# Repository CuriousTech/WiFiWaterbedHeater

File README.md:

# WiFi Smart Waterbed Heater

Discontinued years ago. Go here: [WiFiWaterbedHeater3](https://github.com/CuriousTech/WiFiWaterbedHeater3)

Original model:  

SSR model:

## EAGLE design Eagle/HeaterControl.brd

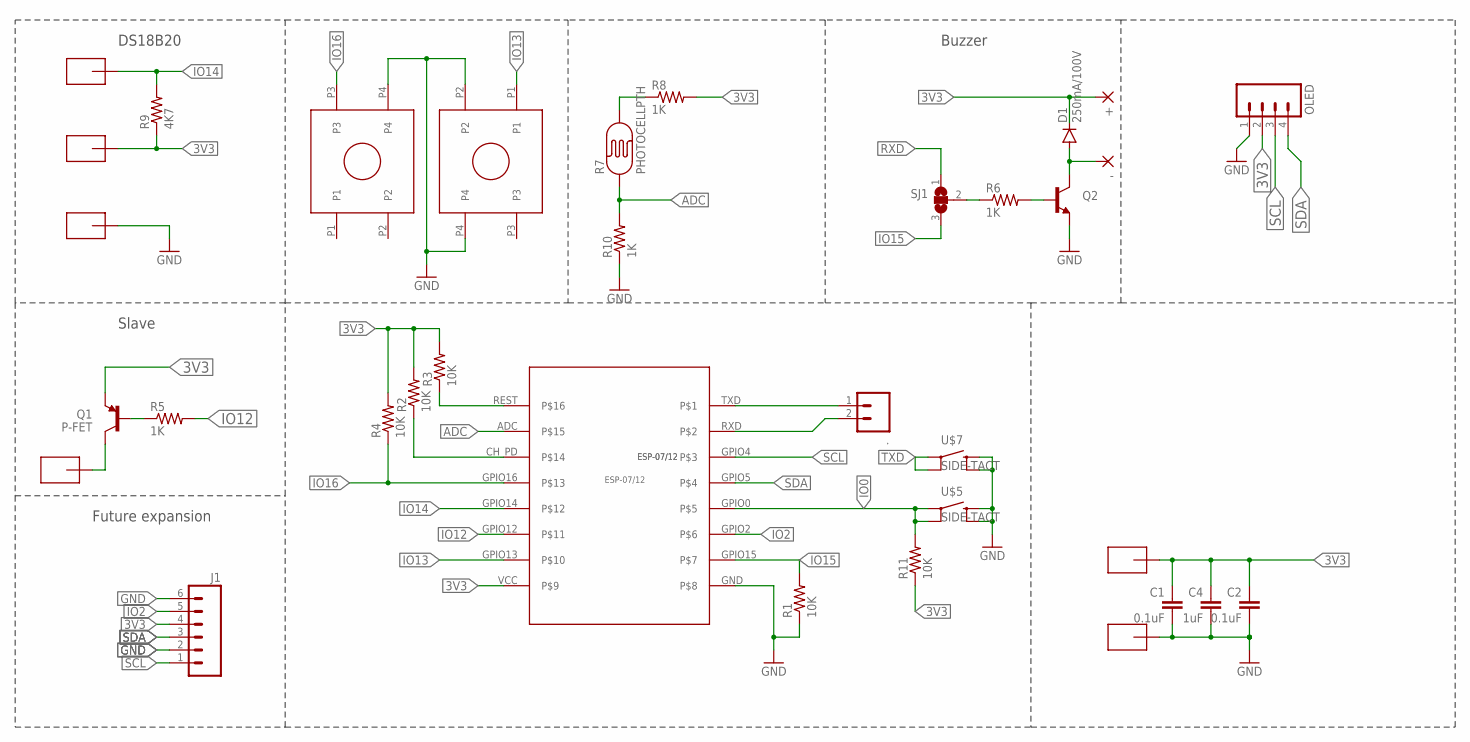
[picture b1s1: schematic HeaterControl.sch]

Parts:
+: 1,6/0,8
-: 1,6/0,8
.: M02PTH; 1X02
C1, C2: 0.1uF; 0805-CAP
C4: 1uF; 0805-CAP
D1: 250mA/100V; SOD-323
J1: M06SILK_FEMALE_PTH; 1X06
LEFT: OMROM_TH
OLED: M04PTH; 1X04
Q1: P-FET; SOT23-3
Q2: TRANSISTOR_NPNSOT23-3; SOT23-3
R1, R2, R3, R4, R11: 10K; 0805
R5, R6, R8, R10: 1K; 0805
R7: PHOTOCELLPTH; PHOTOCELL
R9: 4K7; 0805
RIGHT: OMROM_TH
SJ1: SJ2W; SJ_2
U$1: ESP-07/12
U$2, U$3, U$6, U$8, U$10, U$11: SMD-PAD1
U$5, U$7: SIDE-TACT

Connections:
3V3: +.1, C1.1, C2.1, C4.1, D1.C, J1.4, OLED.2, Q1.2 (E), R2.2, R3.2, R4.2, R8.2, R9.1, R11.1, U$1.VCC, U$3.>NAME, U$8.>NAME
ADC: R7.1, R10.2, U$1.ADC
GND: C1.2, C2.2, C4.2, J1.2, J1.6, LEFT.P4, OLED.1, Q2.2 (E), R1.1, R10.1, RIGHT.P2, RIGHT.P4, U$1.GND, U$5.3 (2), U$5.4, U$6.>NAME, U$7.3 (2), U$7.4, U$11.>NAME
IO0: R11.2, U$1.GPIO0, U$5.1, U$5.2 (3)
IO2: J1.5, U$1.GPIO2
IO12: R5.2, U$1.GPIO12
IO13: RIGHT.P1, U$1.GPIO13
IO14: R9.2, U$1.GPIO14, U$10.>NAME
IO15: R1.2, SJ1.3, U$1.GPIO15
IO16: LEFT.P3, R4.1, U$1.GPIO16
unnamed: Q1.3 (C), U$2.>NAME
unnamed: Q2.1 (B), R6.2
unnamed: -.1, D1.A, Q2.3 (C)
unnamed: R7.2, R8.1
unnamed: Q1.1 (B), R5.1
unnamed: R6.1, SJ1.2
unnamed: R2.1, U$1.CH_PD
REST: R3.1, U$1.REST
RXD: ..2, SJ1.1, U$1.RXD
SCL: J1.1, OLED.3, U$1.GPIO4
SDA: J1.3, OLED.4, U$1.GPIO5
TXD: ..1, U$1.TXD, U$7.1, U$7.2 (3)

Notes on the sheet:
DS18B20
Slave
Buzzer
Future expansion

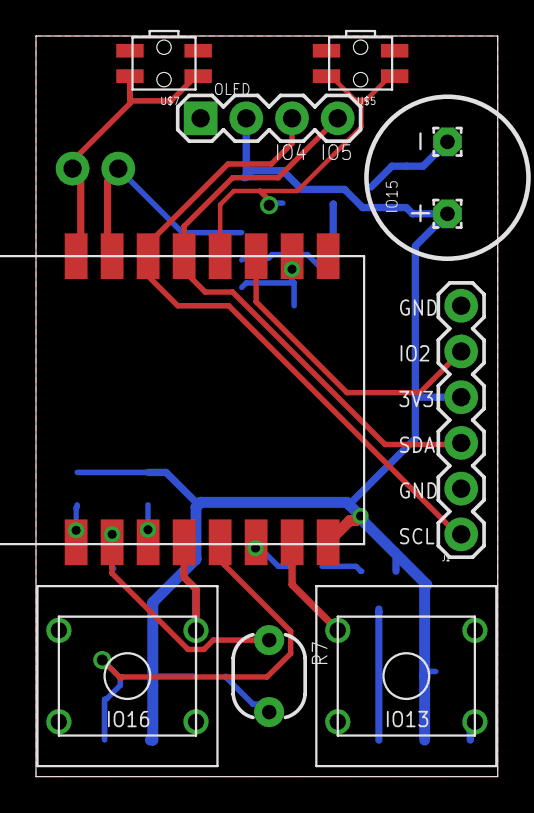
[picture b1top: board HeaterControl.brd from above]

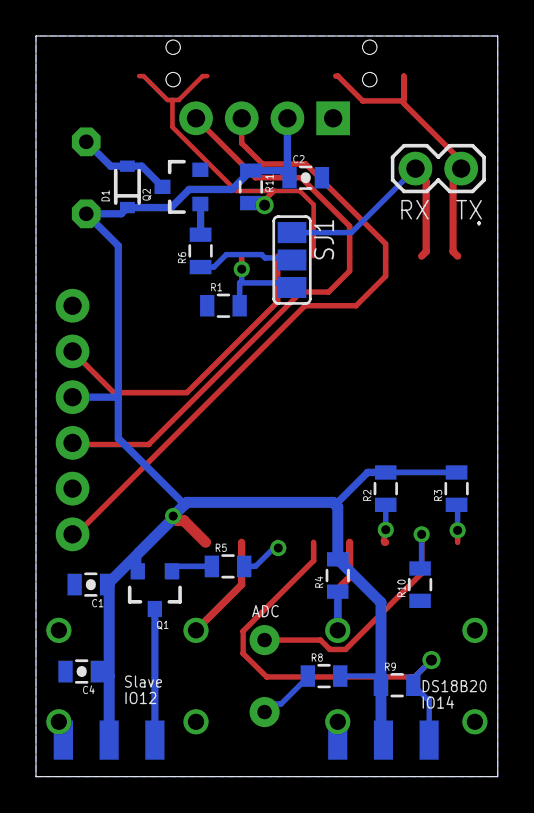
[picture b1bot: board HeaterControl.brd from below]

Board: 2 copper layers, 25.7 x 41.1 mm, 34 parts (24 on the bottom side), 22 nets.

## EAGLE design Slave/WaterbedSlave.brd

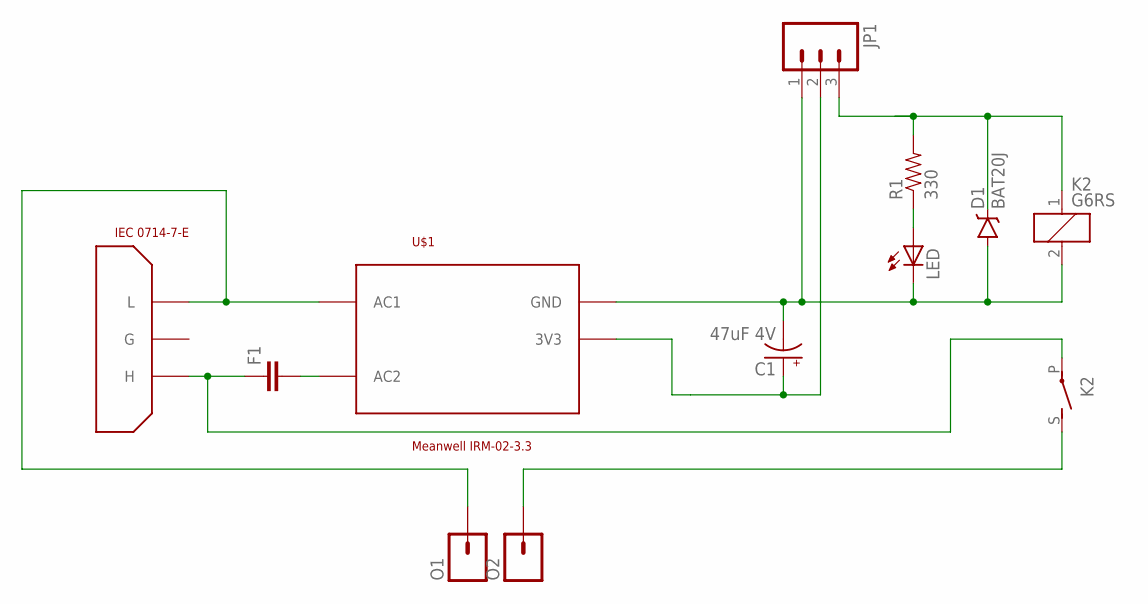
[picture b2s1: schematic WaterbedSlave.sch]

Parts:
C1: 47uF 4V; CPOL-RADIAL-10UF-25V
D1: BAT20J; SOD-323
F1: CAPPTH1; CAP-PTH-5MM
JP1: M03POLAR_LOCK; MOLEX-1X3_LOCK
K2: G6RS
LED: LEDCHIPLED_0805; CHIPLED_0805
O1, O2: M01PTH_2MM; 1X01_2MM
R1: 330; 0805
U$1: Meanwell IRM-02-3.3; RAC02-3.3SC
U$3: IEC 0714-7-E; IEC

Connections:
3V3: C1.1 (+), JP1.2, U$1.GND (3V3)
GND: C1.2 (-), D1.A, JP1.1, K2.2, LED.C, U$1.3V3 (GND)
unnamed: O1.1, U$1.AC1, U$3.L
unnamed: F1.2, U$1.AC2
unnamed: K2.S, O2.1
unnamed: F1.1, K2.P, U$3.H
unnamed: LED.A, R1.1
unnamed: D1.C, JP1.3, K2.1, R1.2

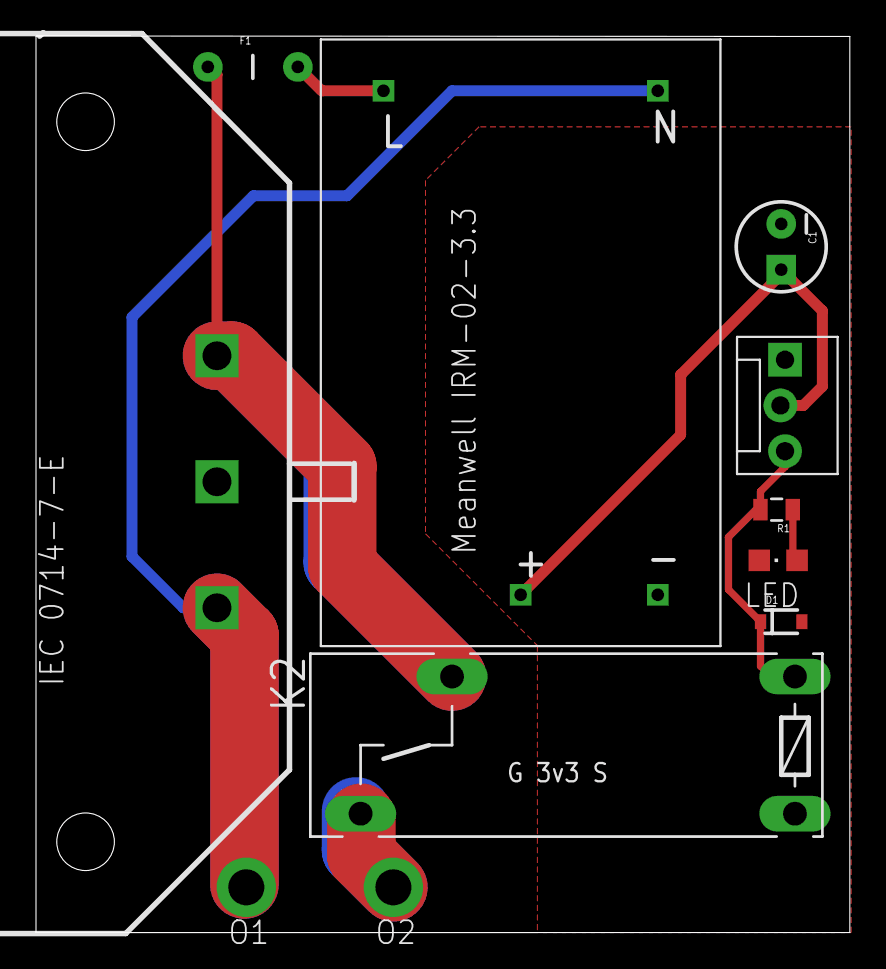
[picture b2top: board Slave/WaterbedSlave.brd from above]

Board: 2 copper layers, 45.2 x 49.8 mm, 11 parts (0 on the bottom side), 8 nets.

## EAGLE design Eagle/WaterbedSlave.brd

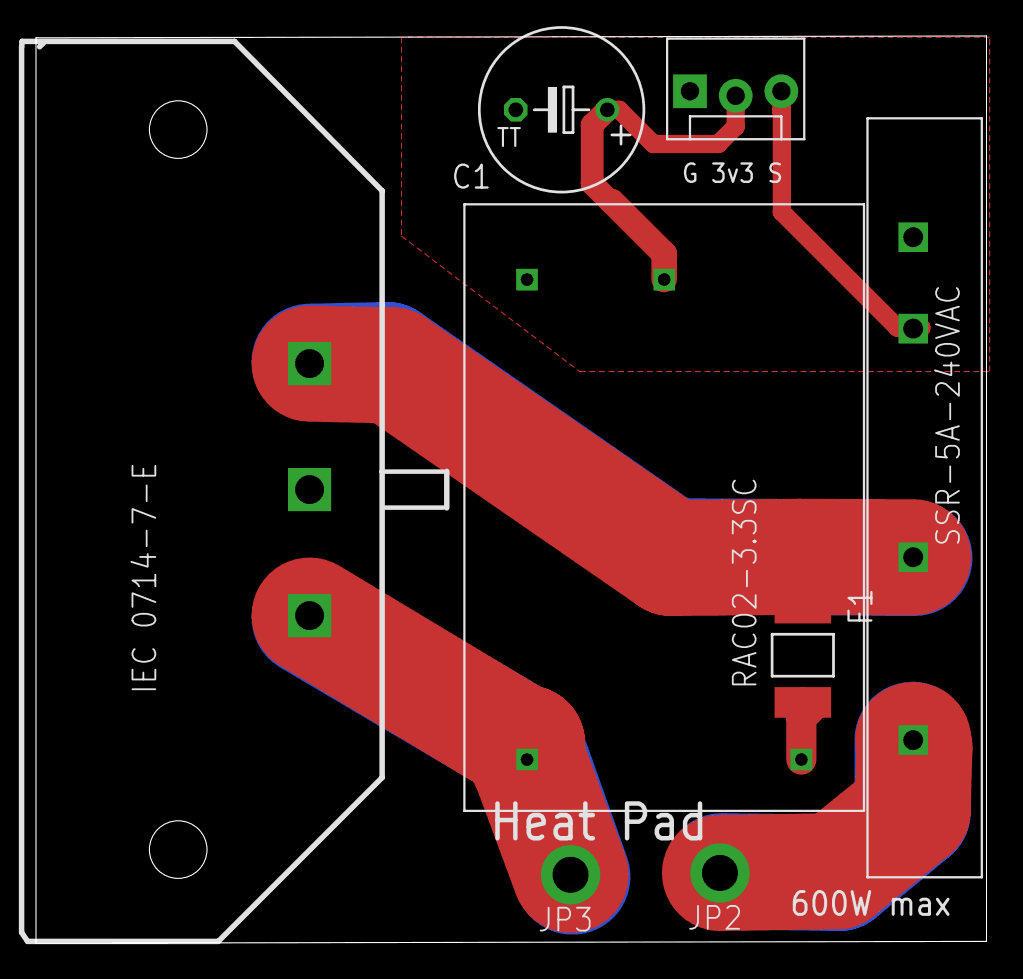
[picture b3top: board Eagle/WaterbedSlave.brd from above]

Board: 2 copper layers, 52.8 x 50.4 mm, 8 parts (0 on the bottom side), 7 nets.

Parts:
C1: 330uF; TT5D9
F1: PTC1812L
JP1: MOLEX-1X3_LOCK
JP2, JP3: 1X01_2MM
SUPP: RAC02-3.3SC
U$2: SSR-5A-240VAC; SIP-4
U$3: IEC 0714-7-E; IEC

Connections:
GND: C1.-, JP1.1, SUPP.3V3, U$2.P$1
unnamed: JP3.1, SUPP.AC1, U$3.L
unnamed: JP2.1, U$2.P$4
unnamed: F1.2, SUPP.AC2
unnamed: F1.1, U$2.P$3, U$3.H
unnamed: C1.+, JP1.2, SUPP.GND
unnamed: JP1.3, U$2.P$2

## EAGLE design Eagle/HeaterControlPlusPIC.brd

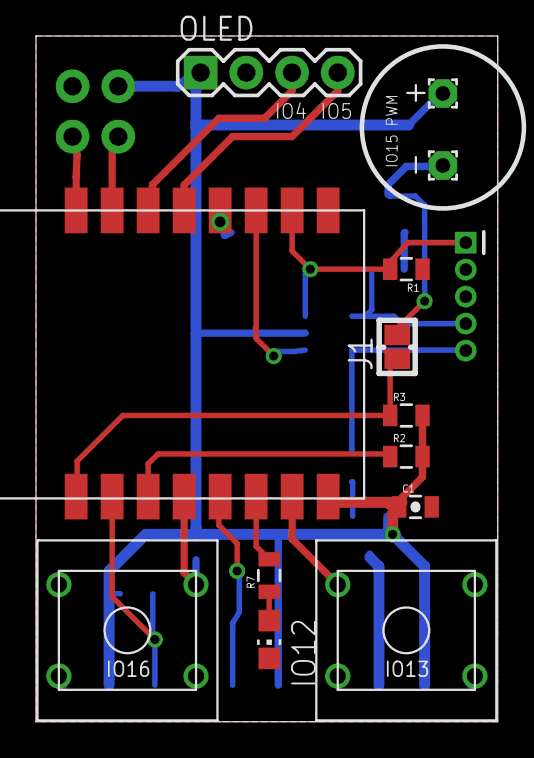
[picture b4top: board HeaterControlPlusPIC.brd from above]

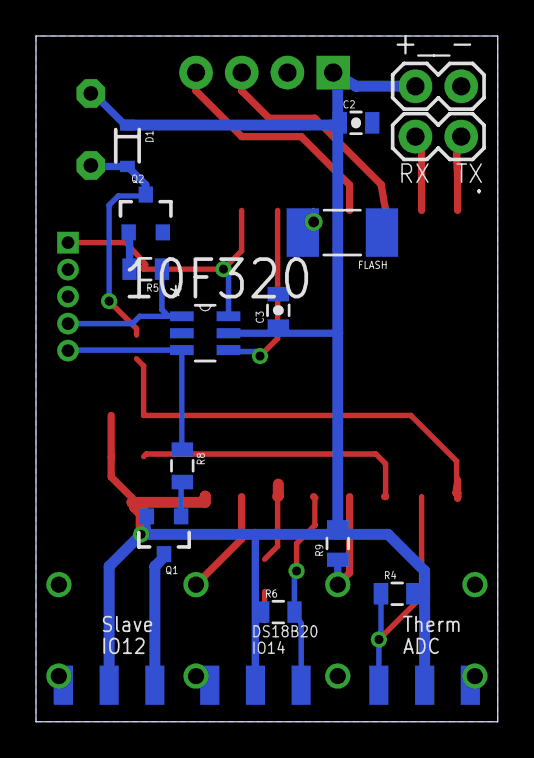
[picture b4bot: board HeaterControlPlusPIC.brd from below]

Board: 2 copper layers, 25.7 x 38.1 mm, 37 parts (23 on the bottom side), 23 nets.

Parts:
10F320: PIC10F320T-I/OT; SOT95P270X145-6N
+: 1,6/0,8
+__-: 1X02
-: 1,6/0,8
.: 1X02
C1, C2, C3: 0.1uF; 0805-CAP
D1: 250mA/100V; SOD-323
FLASH: BTN_4MM
IO12: CHIP-LED0805
J1: JUMPER_SOLDER_1X2
LEFT: OMROM_TH
OLED: 1X04
Q1: P-FET; SOT23-3
Q2: SOT23-3
R1, R2, R3, R4, R8, R9: 10K; 0805
R5: 1K; 0805
R6: 4K7; 0805
R7: 330; 0805
RIGHT: OMROM_TH
U$1: ESP-07/12
U$2, U$3, U$4, U$5, U$6, U$7, U$8, U$10, U$11: SMD-PAD1
U$9: PIC-ICSP-MINI

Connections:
3V3: 10F320.5, +.1, +__-.1, C1.1, C2.1, C3.1, D1.C, OLED.1, Q1.2, R2.2, R3.2, R4.2, R6.1, R9.2, U$1.VCC, U$3.>NAME, U$4.>NAME, U$8.>NAME
ADC: R4.1, U$1.ADC, U$7.>NAME
GND: 10F320.2, +__-.2, C1.2, C2.2, C3.2, FLASH.1, IO12.C, LEFT.P2, LEFT.P4, OLED.2, Q2.2, R1.1, RIGHT.P2, RIGHT.P4, U$1.GND, U$5.>NAME, U$6.>NAME, U$9.3, U$11.>NAME
HEAT: Q1.1, R8.2
ICSPCLK: 10F320.3, R8.1, U$9.5
IO0: FLASH.2, U$1.GPIO0
IO2: 10F320.4, U$1.GPIO2
IO12: R7.2, U$1.GPIO12
IO13: RIGHT.P1, U$1.GPIO13
IO14: R6.2, U$1.GPIO14, U$10.>NAME
IO15: 10F320.6, R1.2, U$1.GPIO15, U$9.1
IO16: LEFT.P3, R9.1, U$1.GPIO16
unnamed: Q1.3, U$2.>NAME
unnamed: Q2.1, R5.2
unnamed: OLED.3, U$1.GPIO4
unnamed: -.1, D1.A, J1.2, Q2.3
unnamed: IO12.A, R7.1
unnamed: OLED.4, U$1.GPIO5
unnamed: R2.1, U$1.CH_PD
PICPWM: 10F320.1, R5.1, U$9.4
REST: J1.1, R3.1, U$1.REST
RXD: ..2, U$1.RXD
TXD: ..1, U$1.TXD

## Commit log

2015-10-30 Rev 1
2015-11-02 Rev 1 buttons/screen aligned
2015-11-06 Fixed backwards supply footprint
2015-11-19 Changed for low on
2015-11-19 Heat low for non-PIC use
2015-11-19 Added jumper for auto-reset
2015-11-19 Cleanup
2015-11-21 Scrolling time
2015-11-23 Added a 14pt proportional font
2015-11-23 Added drawPropString
2015-11-23 Using the new font for the scroller
2015-12-08 Changed PPTC
2015-12-08 Updated PPTC
2015-12-18 Swapped inputs
2015-12-18 Wrong file
2015-12-18 Update for r2 board
2015-12-18 Updated for r2 board
2016-01-05 Better startup
2016-01-09 Turns off if sensor isn't working
2016-01-16 Major update
2016-01-16 Full schedule version.
2016-01-17 Major update rev1
2016-01-17 Fixed tween, all good.
2016-01-22 2 small mistakes
2016-01-31 Smaller blinky dot when display off
2016-02-10 Another 2.0.0 fix
2016-03-04 Added labels to config page
2016-03-12 Changed to event streaming and NTP time
2016-03-13 cleanup, fix DST
2016-03-15 Update for event class
2016-05-05 Added DHT22 to GPIO0
2016-05-05 Fixes for 2.2.0
2016-05-08 Changed JSON names for use as HVAC remote sensor
2016-05-08 Extended IO0, IO2 to side
2016-05-08 Rename Eagle/WaterbedSlave.brd to Slave/WaterbedSlave.brd
2016-05-08 Rename Eagle/WaterbedSlave.sch to Slave/WaterbedSlave.sch
2016-05-21 Page formatting fixes
2016-05-22 Chart for data
2016-06-10 Moved ssd1306 to lib
2016-06-24 Updated page design
2016-06-25 Fix password alert JSON
2016-09-09 Added KWH, cost total
2016-09-14 startEvents() was missing, decimal place fix
2016-09-22 Switched to ESPAsyncWebServer
2016-10-15 Changed to WebSockets
2016-12-15 Changed to js array
2016-12-15 Fixed remote message and beep
2017-01-13 Broke SSID list and change key
2017-01-13 timezone field wrong
2017-01-13 changed path for security
2017-03-02 event keepalive, smoother temps, OTA
2017-03-05 Missing file for SPIFFS
2017-03-05 Canvas added for graphical representation
2017-03-05 Changed web page
2017-03-07 Added temp chart
2017-03-07 Updated web pic
2017-03-09 Skipping for the new format
2017-03-09 Fixed array for the 24hr temps log
2017-03-11 One more temp array tweak
2017-03-11 break the temp line correctly
2017-03-12 Added dynamic range for chart
2017-03-30 Added 12 month display
2017-03-30 Just comments
2017-03-30 comments
2017-04-05 Wrong month cost saved
2017-04-16 Updated to current web GUI
2017-04-18 Updated to latest
2017-04-18 Forgot to update this
2017-04-18 Simplified value tranfsers
2017-05-12 Lost images
2017-07-06 Added more chart gfx
2017-07-06 Fix for printfAll bug
2017-09-21 3D print of control case
2017-09-23 3D printed case for slave board
2017-09-23 Added new cases
2018-05-01 Removed more printfs, added room temp status
2018-05-01 Added favicon
2018-05-01 Added alarm clock data for future use
2018-05-17 Bugfix. cost[-1] memory error
2018-07-28 Slightly smaller old version
2018-07-28 New cheap model
2018-07-30 The cheap AC-DC sucked. Using trusted brand.
2018-09-26 Simple 10A 3V relay version
2018-09-26 Added i2c to side for Am2320
2018-09-26 Backs up current cost sometimes
2018-09-26 added watts, light level for later use
2018-09-26 No events, added watts, light lvl, btn avg adjust
2018-10-13 Added top buttons
2018-10-13 Top button model
2018-10-13 Small fix
2018-10-13 Added force write
2018-10-13 Removed a serial print
2018-10-13 Added buttons, raised vacation range
2018-10-15 Wider lower buttons
2018-10-15 websocket
2018-10-15 watts divide fix
2019-02-21 Cleanup and all up/down
2019-02-21 segmented check
2019-05-15 Added eco switch
2019-05-15 Added eco mode (50% power)
2019-05-15 Added eco mode (50% power) <2.0F diff
2019-05-16 Added eco mode (50% power) <1.0F diff
2019-07-26 Corrected cost calculation
2021-01-23 Copied from new model
2021-01-23 Quite a few changes including ETA
2021-01-23 Add new array
2021-01-23 Changed to watts to secs on
2023-01-26 C++17 compliant
2023-01-26 Merged structs
2023-01-26 Switched to SmartConnect
2023-02-03 Removed json prefix

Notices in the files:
parts and their libraries:
SparkFun-Connectors: Licensing: Creative Commons ShareAlike 4.0 International - https://creativecommons.org/licenses/by-sa/4.0
